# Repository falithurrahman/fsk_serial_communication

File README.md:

#### Description
In this project, i performed serial communication using FSK (Frequency Shift Keying) with the help of IC TCM3105. I will explain you a brief explanation about FSK.

>FSK a frequency modulation scheme in which digital information is transmitted through discrete frequency changes of a carrier signal. The technology is used for communication systems such as telemetry, weather balloon radiosondes, caller ID, garage door openers, and low frequency radio transmission in the VLF and ELF bands. The simplest FSK is binary FSK (BFSK). BFSK uses a pair of discrete frequencies to transmit binary (0s and 1s) information.[2] With this scheme, the "1" is called the mark frequency and the "0" is called the space frequency.

> Source : https://en.wikipedia.org/wiki/Frequency-shift_keying

The board i made was designed using Autodesk EAGLE using one layer printed circuit board. I will call this is *IC TCM3105 Board Module*. The schematic for the board and the board i designed can bee seen at the picture below. I will also attached the .sch and .brd file that i made at PCB folder. Beside the schematic i provide, you can also refer [here](http://www.ne.jp/asahi/hamradio/je9pel/srll_tcm.htm). 

To perform serial communication we need 2 devices, each acts as transmitter and receiver. I will explain each of this device separatedly.
#### 1. Transmitter
In this project i used arduino nano as the microcontroller for transimtter that read the height data received from barometer sensor. The barometer sensor itself used I2C communication. The Tx and Rx pin of arduino nano will be connected to the TxD and RxD of the IC TCM3105 module. TxD and RxD means Transmitter Digital and Receiver Digital. Then the TxA and RxA will transmit the analog modulated signal through active speaker. TxA and RxA means Transmitter Analog and Receiver Analog. I connected active speaker and IC TCM3105 Board using 3.5mm audio jack. *But you have to remember using this method will make around you a little bit noisy.*

#### 2. Receiver
I also used arduino nano connected with IC TCM3105 board for the receiver. The difference is, for the receiver i used pre-amp mic to receive the analog modulated signal that had been sent. This pre-amp mic is connected to the 3.5 audio jack which also connected to TxA and RxA. The TxD and RxD of the IC TCM3105 Module is connected to the Tx and Rx pin of arduino nano. Then for the final step i just need to connect LCD with arduino nano. If everything went well, the data read from barometer at the transmitter would be also available in the LCD of the receiver. 

You can see full diagram block of my project below. The serial communication is done through modulated analog frequency. The board i designed has 3.5 audio jack. If you want the board to act as transmitter just connect active speaker. If you want the board act as receiver just connect pre-amp mic. I only tested one-way communication in this project. I have a plan implementing this project in order to make my own telemetry device. Actually the active speaker and pre-amp mic can be replaced with long range radio device. This will greatly amplify the range of the serial communication. I am very open and if you have any question feel free to ask. Thanks.

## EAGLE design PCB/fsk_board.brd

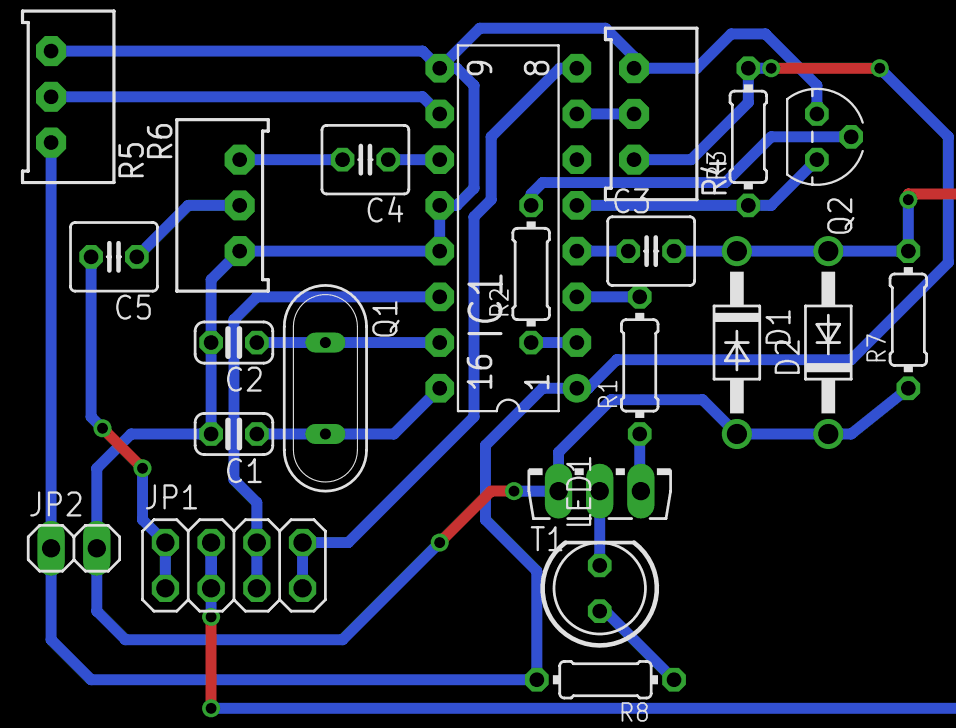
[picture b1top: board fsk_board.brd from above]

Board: 2 copper layers, 22 parts (0 on the bottom side), 21 nets.

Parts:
C1, C2: C025-024X044
C3, C4, C5: C025-040X050
D1, D2: 1N4004; DO41-10
IC1: DIL16
JP1: 2X04
JP2: 1X02
LED1: LED5MM
Q1: QS
Q2: 2N3904; TO92
R1, R2, R3, R7, R8: 0204/7
R4, R5, R6: 3386C
T1: BD139; TO126AV

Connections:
GND: C1.2, C2.2, D1.A, D2.C, IC1.9, IC1.12, IC1.13, JP2.2, Q2.3, R4.1, R5.1, R6.1, R7.1, T1.E
unnamed: IC1.3, R1.2
unnamed: R1.1, T1.B
unnamed: LED1.K, T1.C
unnamed: C2.1, IC1.15, Q1.1
unnamed: C1.1, IC1.16, Q1.2
unnamed: LED1.A, R8.1
unnamed: IC1.2, R2.1
unnamed: Q2.2, R2.2
unnamed: IC1.5, Q2.1, R3.1
unnamed: IC1.7, R4.2
unnamed: IC1.10, R5.2
unnamed: C3.1, IC1.4
unnamed: C4.1, IC1.11
unnamed: C4.2, R6.3
unnamed: C5.1, R6.2
RXA: C3.2, D1.C, D2.A, JP1.3, JP1.4, R7.2
RXD: IC1.8, JP1.7, JP1.8
TXA: C5.2, JP1.1, JP1.2
TXD: IC1.14, JP1.5, JP1.6
VCC: IC1.1, JP2.1, R3.2, R4.3, R5.3, R8.2

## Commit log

2019-10-05 add datasheet
2019-10-10 edit readme
2019-10-10 add picture
2019-10-12 add board
2019-10-12 add code
